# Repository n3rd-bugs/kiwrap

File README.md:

# kiwrap — an AI-agent-facing wrapper over KiCad

**Status: Phase 1c implemented — 2026-09-20.** KiCad 11 (nightly) is the primary target
(decision D16): a headless IPC backend on `kicad-cli api-server` gives structured, data-first
feedback (D17) — board/schematic items, nets, connectivity, ratsnest — and authors schematics
and boards (symbols, wires, labels, power, hierarchical sheets, annotation, footprint
assignment, board setup, netlist sync, placement, zones, routing primitives) with file-tier
and kicad-cli fallbacks on KiCad 10.0.x, 9 and 8. Phase 1c adds **autorouting**
(`kw_pcb_route_auto` / `kw_pcb_fix`: Freerouting 2.4.1 under a managed JRE 25 over a Specctra
DSN/SES round trip — kiwrap's own codec certified against KiCad's exporter/importer, the
patched `kicad-cli pcb export specctra` / `pcb import-ses` on the fork build, mandatory refill +
kicad-cli DRC as the judge), the **JLCPCB fabrication profile** (`kw_fab_export(profile=
"jlcpcb")`, `kw_fab_bom`, `kw_pcb_setup(preset=…)`), **intent** (`kw_intent`, diffed by
`kw_sch_check`) and the **D5 reference board** eval. An agent conversation over MCP stdio
builds a two-sheet LDO + 555 blinker from nothing to gerbers — hand-routed and autorouted — with
ERC 0 / parity 0 / DRC 0 on the 10.99 nightly (ipc11) and 10.0.6 (file)
(tests/test_e2e_authoring.py), and the ESP32-S3 reference board (29 parts, 3 sheets, 2 layers)
from `kw_intent` to a JLCPCB bundle with the grader green — ERC 0, intent diff empty, unrouted
0, must_fix 0 — on both (tests/test_e2e_reference_board.py; numbers below). A source-build
bench of the fork carries the CLI/IPC additions listed in [docs/UPSTREAM.md](docs/UPSTREAM.md).

**Phase 2 (integrated and verified end to end, 2026-09-20): the VS Code extension.** `extension/`
(TypeScript, MIT, a private `.vsix` built by `scripts/build_extension.ps1` into `dist/`) is an MCP
client of its own `kiwrap serve`; it shows **Live KiCad** — the real, sandboxed stock KiCad editors
(10.0.x / 10.99) streamed live into the `.kicad_pcb` / `.kicad_sch` tabs by the Rust helper
`helper/kiwrap-live.exe` (Windows.Graphics.Capture, loopback + token). The user sees the agent's
edits live; to edit by hand they raise KiCad (the tab's *Raise KiCad* button, a double-click) and
work in the real window — decision D20: the live view with native interaction is the product, the
cloaked/injecting modes measured in DISPLAY.md stay parked as experiments. Plus ERC/DRC in the
Problems panel, a KiCad picker and a one-command Claude Code setup. The server side is the
`kw_live` tool (a sandboxed GUI session whose API socket the `ipc11` provider binds to) and the
two-server model: the agent's own `kiwrap serve` finds the extension's session through its record
and writes into the same window — measured in `extension/test/e2e` (12/12 in a real dev host): an
agent's `kw_pcb_place` over a second MCP client repainted the live tab 431-474 ms after the call
started (`kw_pcb_place` 870-979 ms via ipc11), *Raise KiCad* put the real pcbnew / eeschema in the
foreground within ~0.9 s (`GetForegroundWindow`), on 10.99 and on 10.0.6. Details and the numbers:
[docs/EXTENSION.md](docs/EXTENSION.md) (§9.1, §9.2), user guide
[extension/README.md](extension/README.md), the measured display investigation
[docs/DISPLAY.md](docs/DISPLAY.md), screenshots `docs/research/display/img/phase2-*.png`.

kiwrap lets an AI agent (Claude Code inside VS Code; Windows only — decision D18)
do end-to-end electronics development on KiCad — spec → schematic → ERC → board → placement →
routing → DRC → fabrication files — as a wrapper over installed KiCad binaries so KiCad can be
upgraded underneath (7 → 8 → 9 → 10 → 11).

## Quick start (Windows)

```powershell
git clone git@github.com:n3rd-bugs/kiwrap.git; cd kiwrap
.\scripts\bootstrap.ps1          # uv, deps, private JRE 25 + Freerouting into %LOCALAPPDATA%\kiwrap (Linux: scripts/bootstrap.sh)
uv run kiwrap env                # discovered KiCad installs + capability records
uv run pytest -q                 # ~5 min with four KiCads installed; ~1 min without KiCad
uv run kiwrap serve              # MCP server over stdio (Claude Code picks it up from .mcp.json)
.\scripts\build_extension.ps1     # VS Code extension + helper -> dist\kiwrap-<ver>.vsix (needs Node 24 + Rust stable-msvc)
code --install-extension .\dist\kiwrap-0.1.0.vsix   # then "kiwrap: Select KiCad", "kiwrap: Configure Claude Code"
```

Tools (34): `kw_env`, `kw_project` (create / status / retarget / upgrade_preview),
`kw_project_upgrade` (the only conversion of a project to a newer KiCad file format; Claude Code
asks the user on every call), `kw_snapshot`, `kw_job`, `kw_help`,
`kw_live` (launch / attach / status / screenshot / detach / raise a sandboxed GUI KiCad the
extension displays and the `ipc11` provider writes into),
`kw_intent` (declare nets / rails / interfaces; diffed against KiCad's netlist by `kw_sch_check`),
`kw_lib_search` / `kw_lib_info` (FTS index over the sym-/fp-lib-tables), the schematic authoring
tools `kw_sch_add_symbol` (absolute pin endpoints back), `kw_sch_connect`, `kw_sch_add_item`
(power, PWR_FLAG, labels, sheets), `kw_sch_edit`, `kw_sch_annotate`, `kw_sch_assign_footprints`,
the reads `kw_sch_get` (symbols with pin nets, wires, labels, hierarchy, netlist), `kw_sch_stats`,
`kw_sch_check` (ERC + netlist), `kw_sch_diff` (KiCad 11), the board authoring tools
`kw_pcb_setup`, `kw_pcb_sync` (KiCad's netlist, parity-checked), `kw_pcb_place`, `kw_pcb_zones`,
`kw_pcb_route` (track / via primitives with per-net DRC deltas), `kw_pcb_route_auto`
(Freerouting over DSN/SES, a background job with pass / unrouted progress), `kw_pcb_fix` (rip up
the nets of must_fix violations and re-route them until DRC is clean), the reads `kw_pcb_get`
(footprints, pads, tracks, vias, zones, nets, connectivity), `kw_pcb_check` (courtyard overlaps,
off-board, unrouted / ratsnest), `kw_pcb_drc`, `kw_fab_bom`, `kw_fab_export` (generic or the
JLCPCB profile: Protel gerbers, PTH/NPTH drills, corrected CPL, BOM, zip), and the secondary
renders `kw_sch_render` / `kw_pcb_render`. Every tool names its provider (`ipc11`, `file`,
`cli`, `codec`, `cli:<v>+<patch>`) and any degradation. The agent-facing protocol is in
[AGENTS.md](AGENTS.md) and the skill in
[.claude/skills/kiwrap-flow/SKILL.md](.claude/skills/kiwrap-flow/SKILL.md).

**File formats and consent (D21, D24).** A project runs on the installed KiCad that writes its
files' own format. A write that would move the files to a newer format stops with
`E_FORMAT_UPGRADE_REQUIRED`, whose `data.upgrade_args` are the arguments of
`kw_project_upgrade(project, from_kicad, to_kicad, files)`. That tool is published with
`_meta["anthropic/requiresUserInteraction"]: true`, so Claude Code (2.1.199 and later) shows the
user a permission card for every call, whatever the allow rules or permission mode (a headless
session denies it); the VS Code extension's modal calls the same tool. The receipt records which gate and client approved the
call, and its `snapshot_before` undoes the conversion. `scripts/e2e_consent.py` is the manual
end-to-end checklist for that card ([docs/VERIFICATION.md](docs/VERIFICATION.md) claim 13).

## Phase 1c end-to-end numbers (2026-09-20)

Recorded by `tests/test_e2e_reference_board.py` and `tests/test_e2e_authoring.py` (each run
writes `<project>/.kiwrap/e2e-out.json` and `e2e-log.json` with `provider_used` per call):

| flow | KiCad | writes | DSN/SES | router | result |
|---|---|---|---|---|---|
| ESP32-S3 reference board, 29 parts / 52 nets | 10.99.0-4083 | ipc11 (+ file for sheets, no-connects, footprints, setup) | codec | Freerouting 2.4.1, run-dependent: 4 passes, 21.7 s, 221 tracks + 34 vias, 70 -> 0 unrouted (full-suite run); or 18 passes, 12.3 s, 231 + 38, 70 -> 1 (score plateau) and `kw_pcb_fix` 2 rounds (the net alone stalls, the 2 mm neighbourhood closes it) -> 0 | ERC 0, intent diff 0 (strict), parity 0, DRC 0 must_fix / 0 unconnected after refill, grade passed, 18 JLCPCB files, 202-206 tool calls, 4.5-5.4 min |
| ESP32-S3 reference board | 10.0.6 | file | codec | 4 passes, 39.8 s, 217 tracks + 28 vias, 70 -> 0 (full-suite run); or 18 passes, 12.3 s, 204 + 38, 70 -> 1 and `kw_pcb_fix` 1 round -> 0 | ERC 0, intent diff 0, parity 0, DRC 0/0, grade passed, 18 files, 202 tool calls, 2.1 min |
| blinker, 11 parts / 8 nets, autorouted | 10.99.0-4083 | ipc11 | codec | 2 passes, 3.2 s, 37-38 tracks + 5-6 vias, 21 -> 0 unrouted, no fix needed | DRC 0 must_fix / 0 unconnected (1 review: the nightly's own `lib_footprint_mismatch` on import), gerbers + drill + pos, 2.8 min |
| blinker, autorouted | 10.0.6 | file | codec | 2 passes, 3.2 s, 36-37 tracks + 5-6 vias, 21 -> 0 unrouted, no fix needed | DRC 0/0, gerbers + drill + pos, 56 s |
| ecc83 demo stripped to 0 copper (2 and 4 layers), `tests/test_route_auto_providers_live.py` | bench 10.99.0+acdc6a3061 | file | `cli:10.99.0+specctra-jobs` (patched kicad-cli); the codec's DSN == the CLI's | 0 unrouted | DRC 0/0 on both, `kw_pcb_fix` closes two stripped nets through the same chain |

Unrouted is always KiCad's `unconnected_items` count after `pcb drc --refill-zones --save-board`,
never Freerouting's own score. Pour order matters for the router: the B.Cu GND plane before
routing, the F.Cu pour after (docs/ARCHITECTURE.md §8).

## Read in this order

1. [docs/ARCHITECTURE.md](docs/ARCHITECTURE.md) — the decision document: verified capability
   matrix, components, integration strategy per KiCad version, the in-KiCad-plugin and
   source-build decisions, tool catalog, roadmap, risks, §15 decisions, §16 what verification
   changed, §17 known gaps.
2. [docs/DECISIONS.md](docs/DECISIONS.md) — the 15 decisions taken on 2026-09-19 with alternatives and
   consequences, plus D16 (KiCad 11 first) and D17 (data-first feedback, upstream CLI/IPC expansion, source build).
3. [docs/VERIFICATION.md](docs/VERIFICATION.md) — the 12 load-bearing claims (plus claim 13, D24's consent gate), each attacked by an
   empirical and a documentary verifier, with corrections.
4. [CLAUDE.md](CLAUDE.md) — working conventions for anyone (human or agent) changing the code.
5. [docs/research/](docs/research/) — nine research digests and the three competing proposals with
   judge reports; [spikes/](spikes/) — the experiment scripts that produced the evidence.
6. [docs/dev/](docs/dev/) — the KiCad source-build bench (executed), crash symbolication, upstream workflow;
   [docs/LINUX.md](docs/LINUX.md) — what the Linux CI job proves; [docs/UPSTREAM.md](docs/UPSTREAM.md) — gap cards
   and the fork/patch workflow for the KiCad CLI/IPC additions.
7. [docs/EXTENSION.md](docs/EXTENSION.md) — the VS Code extension: processes, channels, security, the
   two-server model, live modes, keybinding policy; [docs/DISPLAY.md](docs/DISPLAY.md) — the measured
   display investigation behind it; [extension/README.md](extension/README.md) — the user guide.

## Layout

```
src/kiwrap/            single MIT distribution (src layout)
  platform/            Windows/Linux seam — the only place that inspects sys.platform
  installation.py      KiCadInstallation + discover()/find()   (registry, Program Files, PATH; Linux: apt/Flatpak/Snap/AppImage)
  capability.py        capability record per FULL semver, seeded from data/kicad_version_matrix.json + --help probes
  sandbox.py           sandboxed KICAD_CONFIG_HOME roots; the user's own KiCad config is read-only (tests assert its hash)
  formats/             zero-dependency: lossless CST, board/schematic models, geometry + analyses (overlaps, connectivity, ratsnest), parsers
  backends/cli/        kicad-cli adapters with the verified quirks (ERC JSON ×100, exit codes, .kicad_prl, out dirs, …) + structured exports
  backends/ipc/        KiCad 11 headless IPC sessions (kicad-python), mm-unit readers, connectivity queries, writes, T5 probe
  core/                MCP server, kw_* tools, receipts/teaching errors, stage machine + gates, locks, snapshots, jobs
conformance/           T1 CST round-trip, T2 file models vs KiCad, T4 kicad-cli help drift, T5 IPC handler snapshot, T6 quirks, T7 IPC writes + Specctra codec vs KiCad's DSN/SES, T8 writers vs KiCad + corpus
tests/                 unit + live tests (auto-skip without KiCad)
extension/             the VS Code extension (TypeScript, MIT): MCP client of `kiwrap serve`, Live KiCad tabs, Problems panel, Configure Claude Code
helper/                Rust workspace (MIT): kiwrap-live.exe, the Windows.Graphics.Capture + input helper the extension bundles
scripts/               bootstrap.ps1 / bootstrap.sh, build_extension.ps1 (-> dist/*.vsix), engines.json (pinned JRE/Freerouting), seed_config_root.py, ci/, dev/
```

## Shape of the design (one paragraph)

One Python MCP server (`kiwrap-core`, `kw_*` tools) is the only agent contract; a thin
TypeScript VS Code extension is a client of it (its own instance; the agent runs another, both
sharing the storage home and the per-project lock), shows the sandboxed KiCad GUI that `kw_live`
launched inside VS Code tabs through a Rust capture helper, and feeds ERC/DRC into the Problems
panel; the `KiWrap Connect` KiCad plugin of the Phase-0 plan is not needed while `kw_live` owns
the GUI it displays. On KiCad 11 the primary backend is the headless IPC API (`kicad-cli
api-server`, driven through kicad-python): structured reads of every board and schematic item,
connectivity, netlist and hierarchy, and writes as undoable commits. Underneath sits an in-house
lossless s-expression engine that models boards and schematics on every version 7–11 (pin
endpoints, courtyards, zone fills, connectivity, a ratsnest estimate verified against KiCad's own
DRC) and is the only schematic path on ≤ 10. ERC/DRC/exports come exclusively from `kicad-cli` —
KiCad is the judge. Routing will be Freerouting 2.4.1 over DSN/SES (managed JRE 25). Every tool
answers in millimetres with its provider (`ipc11`, `file`, `cli`) and any degradation named; stage
gates (ERC → sync → place → route → DRC → fab) are server-enforced. Where KiCad exposes no
structured surface (ratsnest export, DRC/ERC over the API, headless jobs) the private fork
`n3rd-bugs/kicad-fork` carries the additions until they are merged upstream.

## Local environment this was verified on

Windows 11; KiCad 7.0.6, 8.0.9, 9.0.9, 10.0.6 and the 10.99 nightly (10.99.0-4083, KiCad 11
preview) side by side under `C:\Program Files\KiCad`, plus the registered source builds under
`C:\kiwrap-builds`; Python 3.11 + uv; Node 24 LTS and Rust 1.95 stable-msvc (the extension build);
VS Code 1.138; Java 17 on PATH (Freerouting 2.4.1 needs 25 → managed JRE); VS 2022 17.14 (MSVC
14.44) + vcpkg for the KiCad source bench; `cdb` from the Windows 10 SDK. Linux code paths exist behind the platform seam
but are out of scope (D18).

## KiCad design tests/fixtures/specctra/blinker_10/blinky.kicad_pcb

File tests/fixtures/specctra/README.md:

# Specctra codec fixtures

`blinker_10/` — the Phase 1b LDO + 555 blinker board (`tests/test_e2e_authoring.py`) as the agent
flow left it on KiCad 10.0.6: 11 footprints (SMD + THT), 8 nets, 24 routed segments, a GND pour on
both layers, netclass patterns in the `.kicad_pro` (whose `net_settings.meta.version` is 0, so
KiCad drops the patterns on load — see `kiwrap.formats.specctra.rules`). Used by
`tests/test_specctra_*.py` offline and by `conformance/tests/t7_specctra_codec.py` as the board
that is stripped, routed by Freerouting, applied through the codec and judged by kicad-cli DRC.

KiCad's own demo boards (ecc83, kit-dev-coldfire-xilinx_5213, openair-max) are copied from
`<install>/share/kicad/demos` at test time and are not committed (conformance corpus rule).

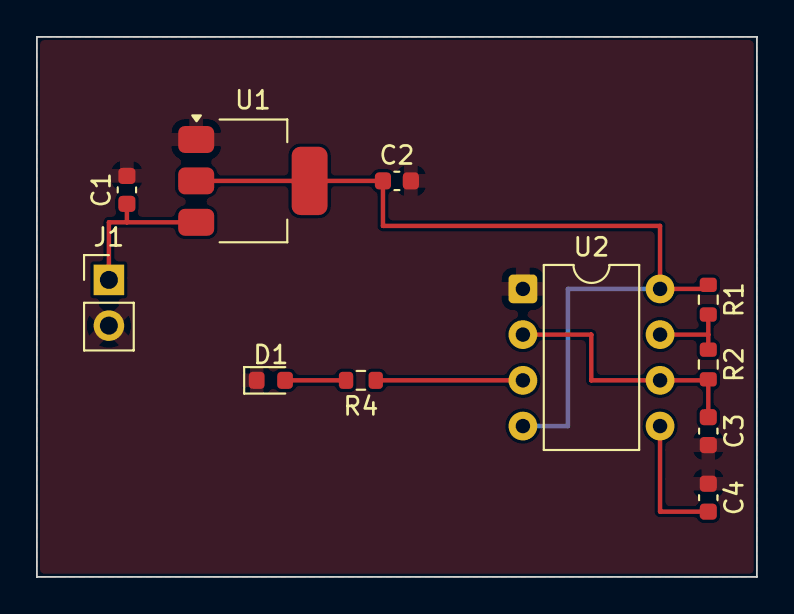
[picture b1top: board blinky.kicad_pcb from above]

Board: 2 copper layers, 40.0 x 30.0 mm, 11 parts (0 on the bottom side), 8 nets.

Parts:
C1, C2, C3: 10u; C_0603_1608Metric
C4: 10n; C_0603_1608Metric
D1: RED; LED_0603_1608Metric
J1: VIN; PinHeader_1x02_P2.54mm_Vertical
R1: 1k; R_0603_1608Metric
R2: 10k; R_0603_1608Metric
R4: 330; R_0603_1608Metric
U1: AMS1117-3.3; SOT-223-3_TabPin2
U2: NE555P; DIP-8_W7.62mm

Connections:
+3V3: C2.1, R1.1, U1.2 (VO), U2.4 (~RST), U2.8 (VCC)
/VIN: C1.1, J1.1, U1.3 (VI)
/blinker/BLINK: R4.1, U2.3 (OUT)
GND: C1.2, C2.2, C3.2, C4.1, D1.1 (K), J1.2, U1.1 (GND), U2.1 (GND)
unnamed: D1.2 (A), R4.2
unnamed: C4.2, U2.5 (CONT)
unnamed: R1.2, R2.1, U2.7 (DISCH)
unnamed: C3.1, R2.2, U2.2 (TRIG), U2.6 (THRES)

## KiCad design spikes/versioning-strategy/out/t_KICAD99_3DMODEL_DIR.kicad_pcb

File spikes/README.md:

# Spikes — experiment scripts from the research phase

These are the scripts the research and verification agents actually ran on 2026-09-18 against the
installed KiCad 7.0.6 / 8.0.1 / 9.0.5 / 10.0.0 (plus Freerouting 2.4.1, kicad-python 0.8.0, mcp 2.2).
They are preserved verbatim (paths inside them still point at the original scratchpad; large
binaries, venvs, JREs, PDB caches and cloned repos were not copied). They are the seed corpus for
the conformance suite (T1–T9 in `docs/ARCHITECTURE.md` §6) and the fastest way to reproduce any
finding in `docs/research/` or `docs/VERIFICATION.md`.

| Folder | What it proves |
|---|---|
| `ipc-api/`, `verify-gui-api/`, `verify-ipc-config-home/`, `verify-sch-ipc/`, `verify-24966/` | IPC API live tests, config-home seeding, the eeschema handler crash (#24966), handler inventories 10 vs master |
| `swig-pcbnew/`, `verify-headless-board/`, `verify-headless-build/` | Headless board build / zone fill / save under each version's bundled python; the driver checklist |
| `schematic-authoring/`, `erc_verify/`, `verify-sch-20260306/`, `pin-orient-verify/`, `verify-pin-orient/`, `erc-json-scale/`, `verify-erc-json-units/` | Hand-written `.kicad_sch` generator (`gen.py` + `sexp.py`) that passes kicad-cli 10 ERC; the 12-orientation pin transform; the ERC JSON ×100 bug |
| `autorouting/`, `freerouting-verify/`, `verify-freerouting/`, `specctra-verify/`, `verify-specctra/` | DSN export → Freerouting 2.4.1 → SES import round trips, flag experiments, KiCadRoutingTools |
| `versioning-strategy/`, `fmt-compat/`, `verify-format-compat/`, `verify-cli-api/`, `verify-cli-api-claim/` | Format stamps per version, cross-version load matrix, kicad-cli flag drift 7→10 |
| `mcp-verify/`, `verify-mcp22/`, `vscode-agent-surface/` | mcp 2.2 server returning PNG ImageContent over stdio and streamable HTTP |
| `verify-symbols/`, `verify-symbols-pdb/` | cdb + symbols.kicad.org symbolication of KiCad crash dumps (no source build) |
| `kicad-plugin-and-build/`, `prior-art/`, `e2e-agent-workflow/` | Plugin mechanisms, source-build research, prior-art survey notes, tool-catalog derivation |

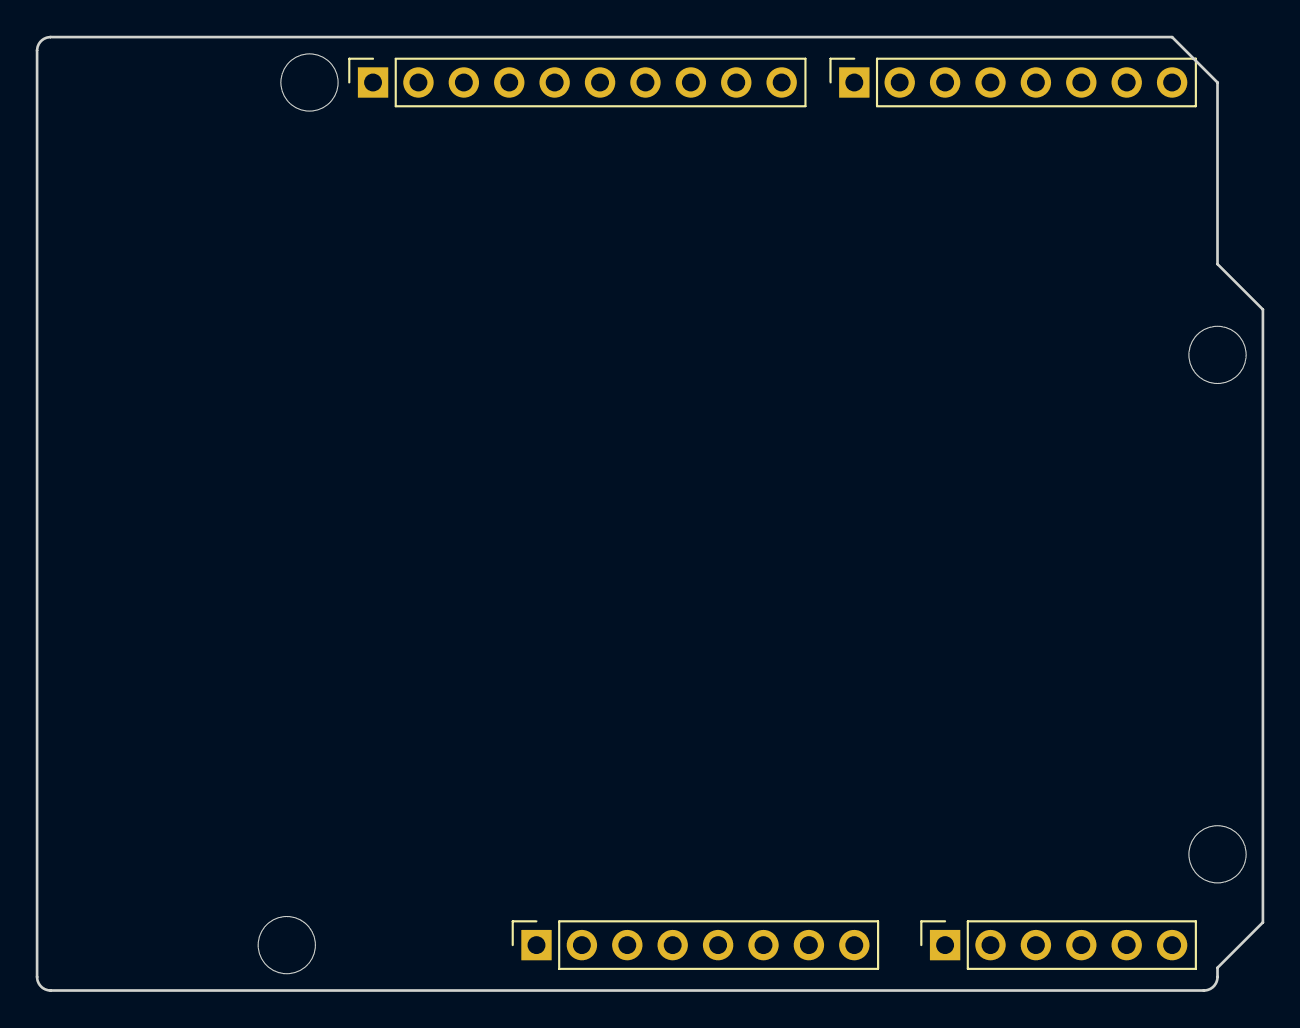
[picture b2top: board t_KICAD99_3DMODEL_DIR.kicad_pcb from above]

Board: 2 copper layers, 68.6 x 53.3 mm, 8 parts (0 on the bottom side), 3 nets, no tracks yet.

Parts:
J1: Power; PinSocket_1x08_P2.54mm_Vertical
J2: Digital/PWM; PinSocket_1x10_P2.54mm_Vertical
J3: Analog; PinSocket_1x06_P2.54mm_Vertical
J4: Digital/PWM; PinSocket_1x08_P2.54mm_Vertical
MH1, MH2, MH3, MH4: MountingHole_3.2mm

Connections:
/SCL/A5: J2.1, J3.6
/SDA/A4: J2.2, J3.5
GND: J1.6, J1.7, J2.4
